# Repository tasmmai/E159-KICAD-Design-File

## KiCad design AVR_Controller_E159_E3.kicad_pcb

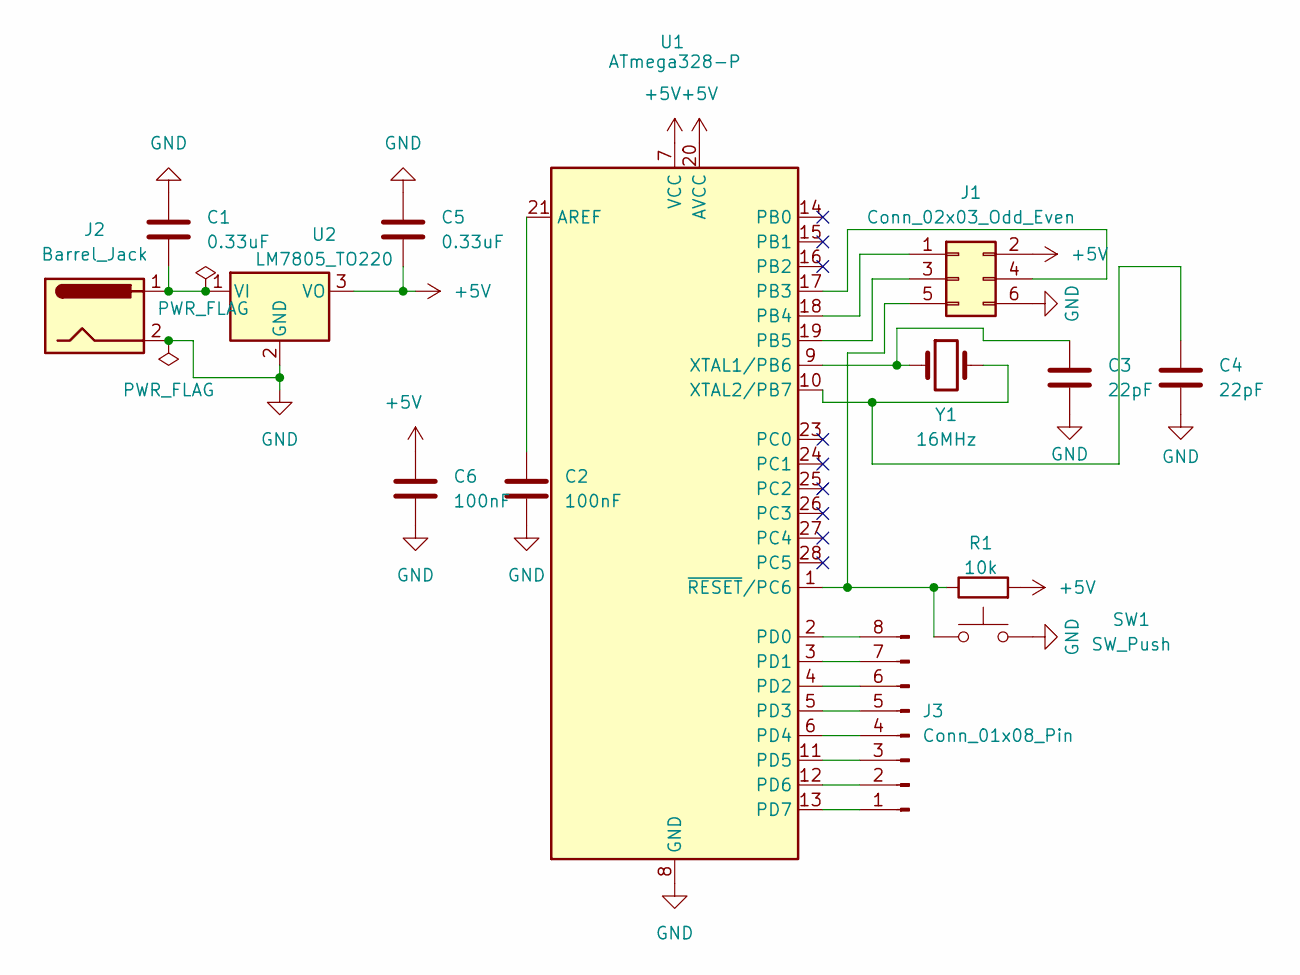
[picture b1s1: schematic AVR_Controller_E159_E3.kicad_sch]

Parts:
C1, C5: 0.33uF; C_Disc_D5.0mm_W2.5mm_P5.00mm
C2, C6: 100nF; C_Disc_D5.0mm_W2.5mm_P5.00mm
C3, C4: 22pF; C_Disc_D5.0mm_W2.5mm_P5.00mm
J1: Conn_02x03_Odd_Even; PinHeader_2x03_P2.54mm_Vertical
J2: Barrel_Jack; BarrelJack_Horizontal
J3: Conn_01x08_Pin; PinHeader_1x08_P2.54mm_Vertical
R1: 10k; R_Axial_DIN0207_L6.3mm_D2.5mm_P10.16mm_Horizontal
SW1: SW_Push; SW_PUSH_6mm
U1: ATmega328-P; DIP-28_W7.62mm
U2: LM7805_TO220; TO-220-3_Vertical
Y1: 16MHz; Crystal_HC49-4H_Vertical

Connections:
+5V: C5.2, C6.2, J1.2, R1.2, U1.7 (VCC), U1.20 (AVCC), U2.3 (VO)
GND: C1.1, C2.1, C3.2, C4.2, C5.1, C6.1, J1.6, J2.2, SW1.2, U1.8 (GND), U1.22 (GND), U2.2 (GND)
unnamed: J1.1, U1.18 (PB4)
unnamed: J1.3, U1.19 (PB5)
unnamed: J1.4, U1.17 (PB3)
unnamed: J1.5, R1.1, SW1.1, U1.1 (~RESET/PC6)
unnamed: J3.1, U1.13 (PD7)
unnamed: J3.2, U1.12 (PD6)
unnamed: J3.3, U1.11 (PD5)
unnamed: J3.4, U1.6 (PD4)
unnamed: J3.5, U1.5 (PD3)
unnamed: J3.6, U1.4 (PD2)
unnamed: J3.7, U1.3 (PD1)
unnamed: J3.8, U1.2 (PD0)
unnamed: C2.2, U1.21 (AREF)
unnamed: C3.1, U1.9 (XTAL1/PB6), Y1.1
unnamed: C4.1, U1.10 (XTAL2/PB7), Y1.2
unnamed: C1.2, J2.1, U2.1 (VI)

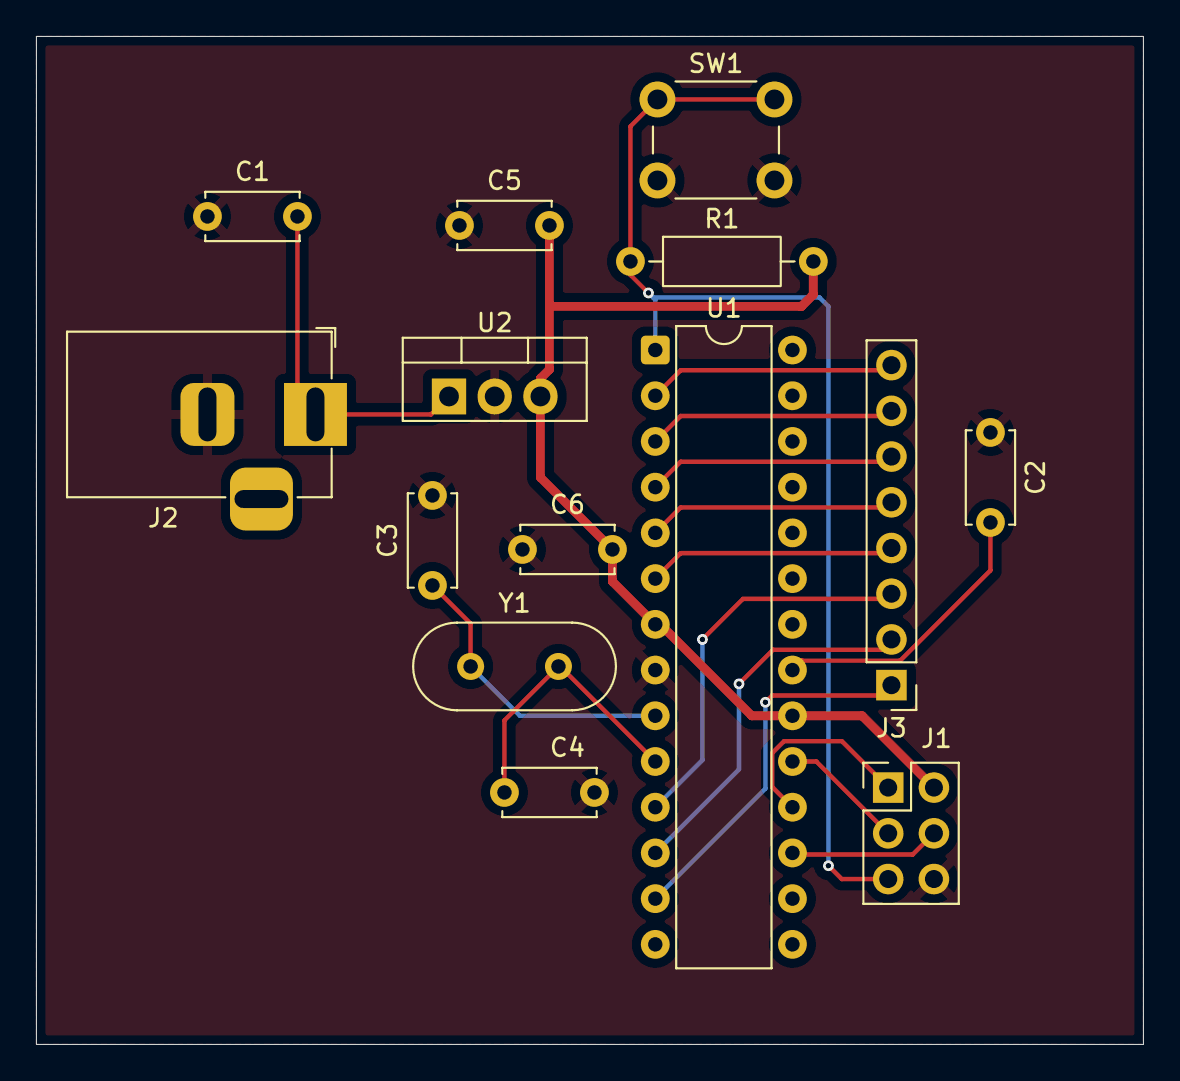
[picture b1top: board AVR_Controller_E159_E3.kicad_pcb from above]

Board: 2 copper layers, 61.5 x 56.0 mm, 14 parts (0 on the bottom side), 18 nets.

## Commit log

2026-03-10 Uploaded Files for KICAD Submission
